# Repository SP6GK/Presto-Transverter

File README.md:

# Presto — QO-100 Transverter

**Status: Work in Progress — October 2026**

Presto is a modular transverter designed to enable communication via the QO-100 satellite using a standard 10 m capable HF transceiver. It provides a 2.4 GHz S-band uplink and downconverts the Ku-band LNB signal for reception on an HF transceiver.

This project includes the schematic and PCB design files, organized under the `ECAD/` directory.
`Documents/` includes interactive BOM and .pdf schematic.

## Features

- **RF signal quality:** Multi-stage frequency conversion, filtering, and high linearity mixers to minimize spurious emissions.
- **Modular hardware:** Replaceable local oscillator modules, a dedicated control head, and extensive RF shielding.
- **LNB front end:** Band pass filtering, attenuation, a bypassable LNA, an integrated downconverter, and an output for an external SDR.
- **LNB control:** Programmable bias-T voltage for polarization selection.
- **Embedded firmware:** STM32F411 microcontroller running C with FreeRTOS.
- **Graphical interface:** Frequency control, configuration menus, and diagnostic information.
- **Remote control:** B.A.S.I.C. (Basic Automated SCPI Interpreter for Controllers) provides serial control through SCPI-like commands.
- **Built-in diagnostics:** Startup and runtime self-tests, error logging, memory integrity checks, and automatic gain control.
- **Calibration tools:** Python scripts and service commands for EEPROM programming and automated calibration.

## System and compatibility
This repository contains all documentation for the motherboard of Presto transverter. Complete system consists also requires:
- **Control Head** Contains mcu with software and HID
- **2 x LO Module** LMX2572 LP based local oscillator module
Repositories for above modules are coming soon

## Project Status

**This project is actively under development and is not yet complete.**
Currently the RF path is under evaluation and characterization.

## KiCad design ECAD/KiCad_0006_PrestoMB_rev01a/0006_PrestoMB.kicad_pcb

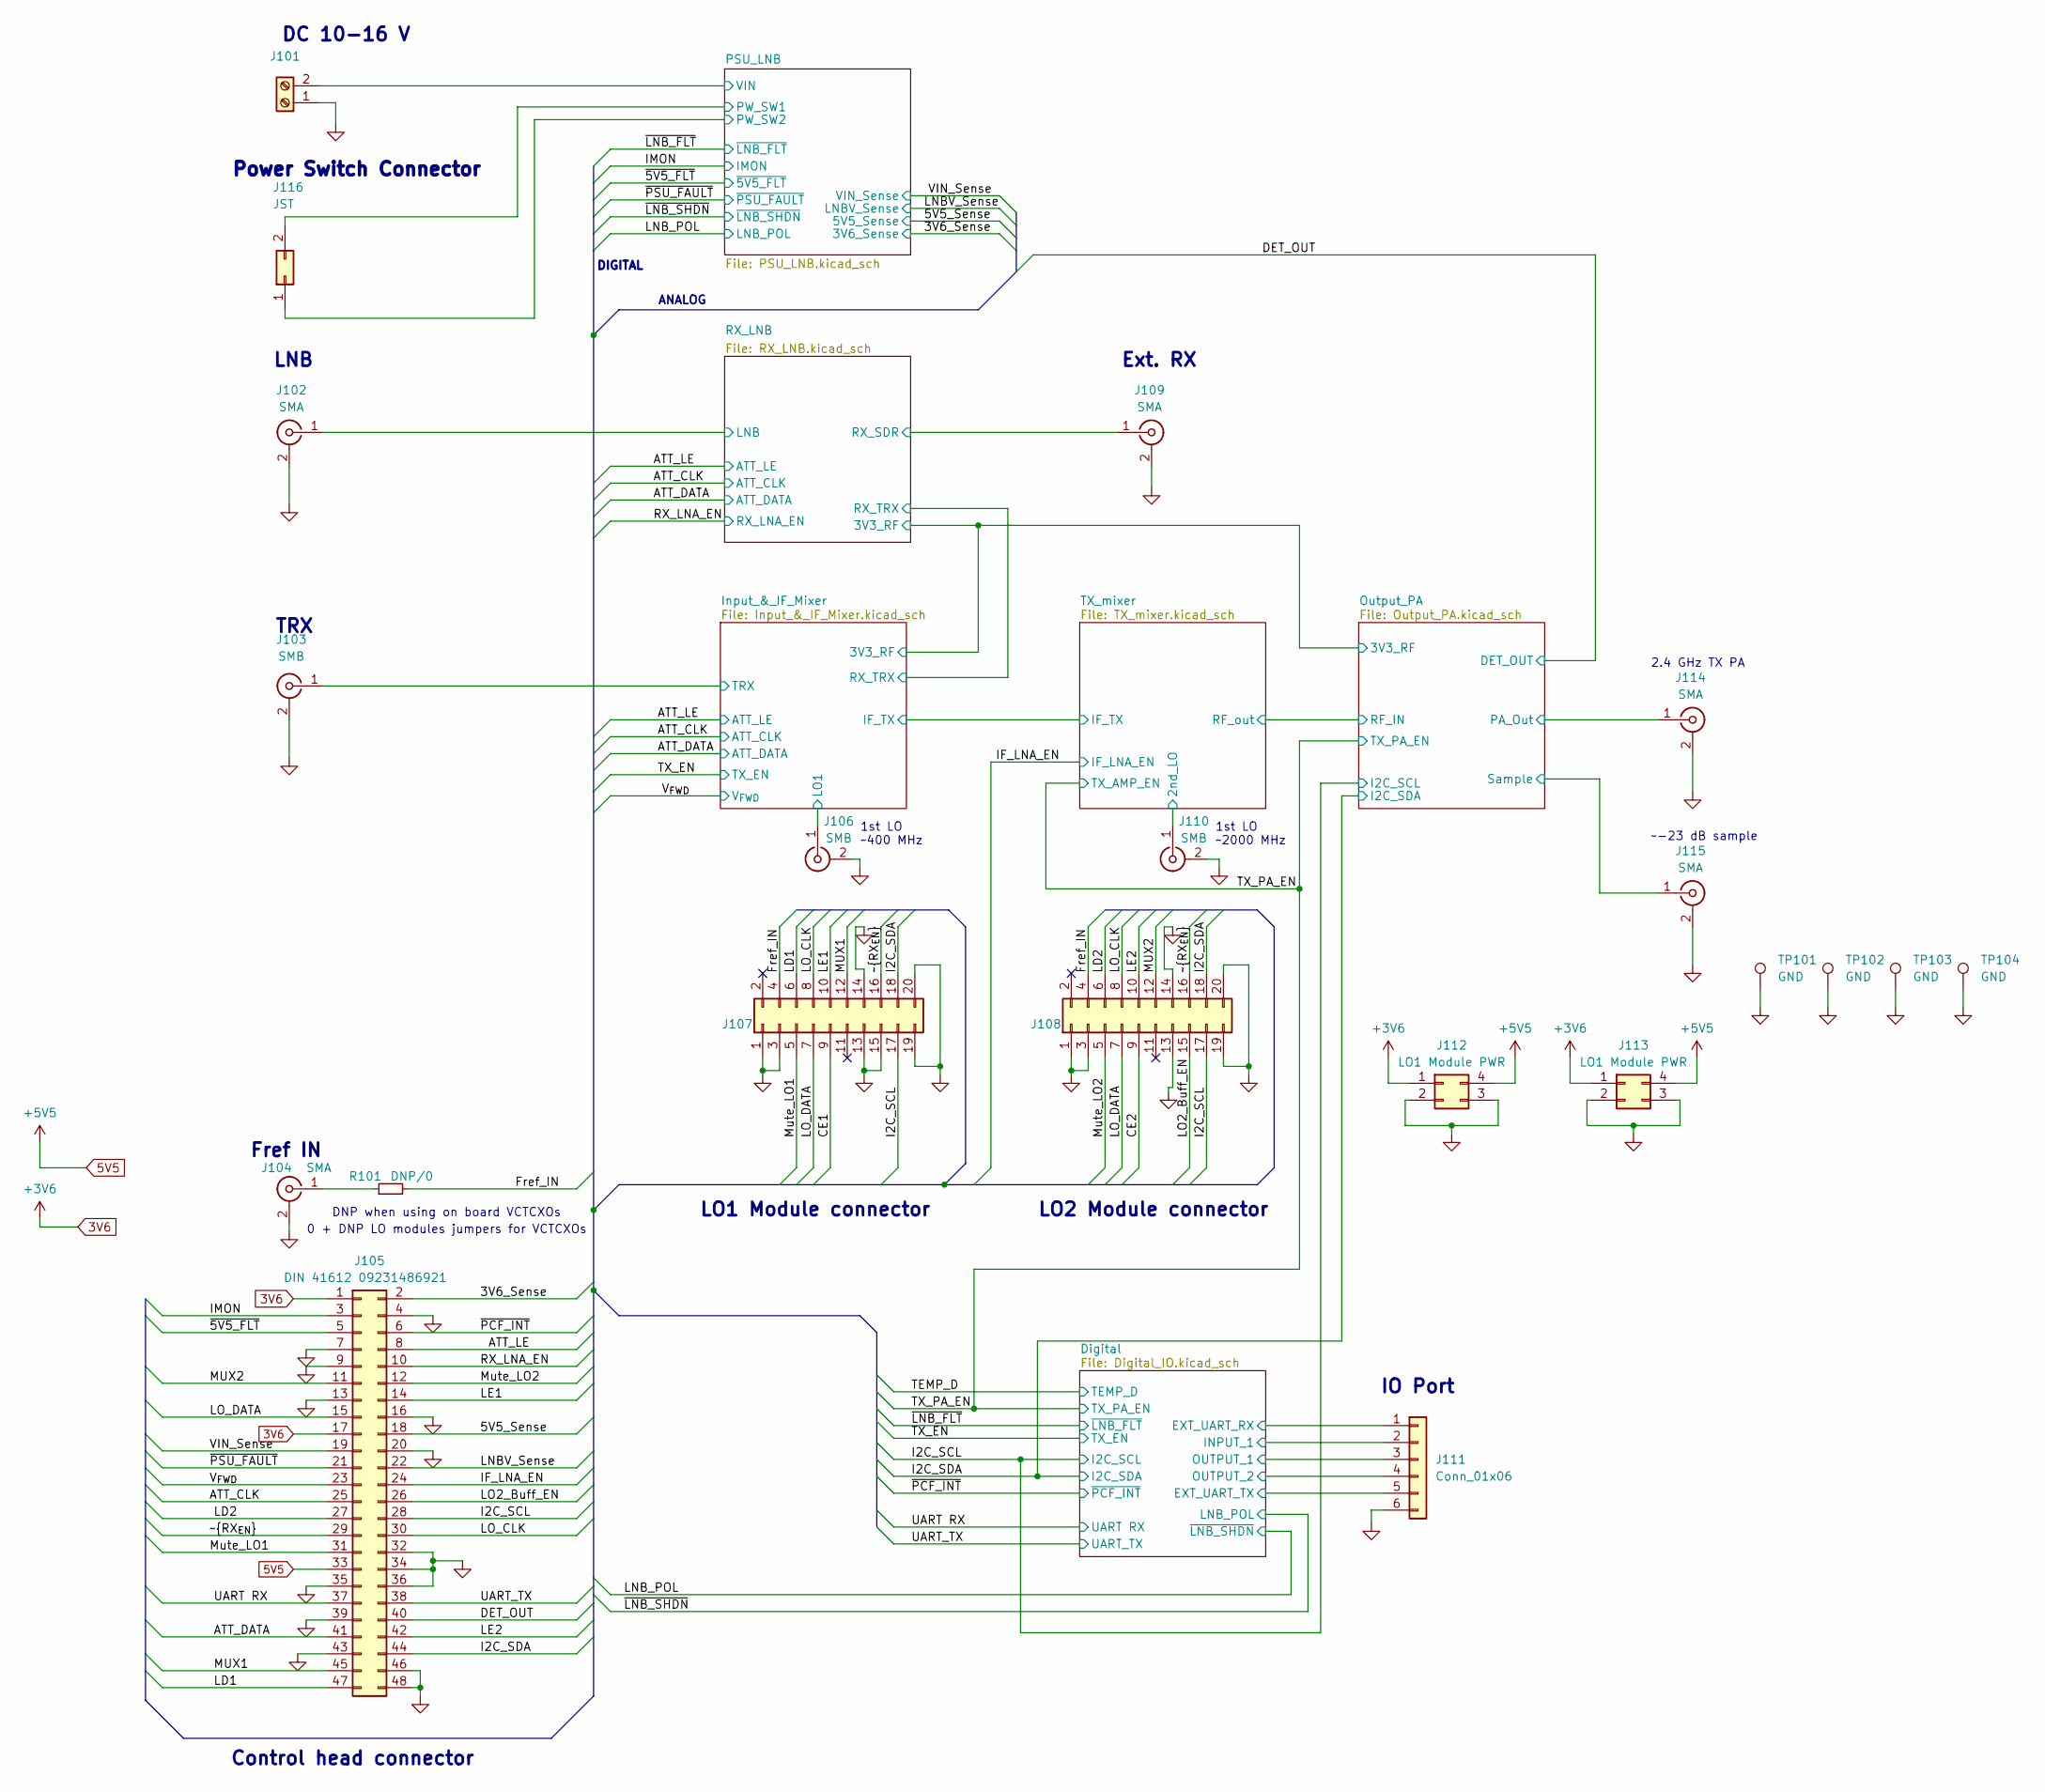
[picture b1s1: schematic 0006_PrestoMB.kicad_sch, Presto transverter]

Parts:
J101: Screw_Terminal_01x02; TerminalBlock_bornier-2_P5.08mm
J102, J114, J115: SMA; SMA_Samtec_SMA-J-P-H-ST-EM1_EdgeMount
J103, J106, J110: SMB; SMB_Jack_Vertical
J104, J109: SMA; SMB_Jack_Vertical
J105: DIN 41612 09231486921; DIN_41612_48Pin_90angle_Male_09231486921HARTING
J107, J108: LO1 Connector; PinHeader_2x10_P2.54mm_Vertical
J111: Conn_01x06; JST_EH_B6B-EH-A_1x06_P2.50mm_Vertical
J112, J113: LO1 Module PWR; PinHeader_2x02_P2.54mm_Vertical
J116: JST; JST_EH_B2B-EH-A_1x02_P2.50mm_Vertical
R101: DNP/0; R_1206_3216Metric_Pad1.30x1.75mm_HandSolder
TP101, TP102, TP103, TP104: GND; TestPoint_Pad_D4.0mm

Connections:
3V6: J105.1, J105.17, J112.1, J113.1; also elsewhere on the board
5V5: J105.33, J112.4, J113.4; also elsewhere on the board
/3V6_Sense: J105.2; also elsewhere on the board
/5V5_Sense: J105.18; also elsewhere on the board
/ATT_CLK: J105.25; also elsewhere on the board
/ATT_DATA: J105.41; also elsewhere on the board
/ATT_LE: J105.8; also elsewhere on the board
/CE1: J107.9
/CE2: J108.9
/DET_OUT: J105.40; also elsewhere on the board
/Digital/EXT_UART_RX: J111.1; also elsewhere on the board
/Digital/EXT_UART_TX: J111.5; also elsewhere on the board
/Digital/INPUT_1: J111.2; also elsewhere on the board
/Digital/OUTPUT_1: J111.3; also elsewhere on the board
/Digital/OUTPUT_2: J111.4; also elsewhere on the board
/Fref_IN: J107.4, J108.4, R101.2
/I2C_SCL: J105.28, J107.17, J108.17; also elsewhere on the board
/I2C_SDA: J105.44, J107.18, J108.18; also elsewhere on the board
/IF_LNA_EN: J105.24; also elsewhere on the board
/IMON: J105.3; also elsewhere on the board
/Input_&_IF_Mixer/LO1: J106.1 (In); also elsewhere on the board
/Input_&_IF_Mixer/TRX: J103.1 (In); also elsewhere on the board
/LD1: J105.47, J107.6
/LD2: J105.27, J108.6
/LE1: J105.14, J107.10
/LE2: J105.42, J108.10
/LNBV_Sense: J105.22; also elsewhere on the board
/LO2_Buff_EN: J105.26, J108.15
/LO_CLK: J105.30, J107.8, J108.8
/LO_DATA: J105.15, J107.7, J108.7
/MUX1: J105.45, J107.12
/MUX2: J105.11, J108.12
/Mute_LO1: J105.31, J107.5
/Mute_LO2: J105.12, J108.5
/Output_PA/PA_Out: J114.1 (In); also elsewhere on the board
/Output_PA/Sample: J115.1 (In); also elsewhere on the board
/PSU_LNB/PW_SW1: J116.2; also elsewhere on the board
/PSU_LNB/PW_SW2: J116.1; also elsewhere on the board
/PSU_LNB/VIN: J101.2; also elsewhere on the board
/RX_LNA_EN: J105.10; also elsewhere on the board
/RX_LNB/LNB: J102.1 (In); also elsewhere on the board
/RX_LNB/RX_SDR: J109.1 (In); also elsewhere on the board
/TX_mixer/2nd_LO: J110.1 (In); also elsewhere on the board
/UART RX: J105.37; also elsewhere on the board
/UART_TX: J105.38; also elsewhere on the board
/VIN_Sense: J105.19; also elsewhere on the board
/V_{FWD}: J105.23; also elsewhere on the board
/~5V5_FLT: J105.5; also elsewhere on the board
/~PCF_INT: J105.6; also elsewhere on the board
/~PSU_FAULT: J105.21; also elsewhere on the board
/~RX_{EN}: J105.29, J107.16, J108.16
GND: J101.1, J102.2 (Ext), J103.2 (Ext), J104.2 (Ext), J105.4, J105.7, J105.9, J105.13, J105.16, J105.20, J105.32, J105.34, J105.35, J105.36, J105.39, J105.43, J105.46, J105.48, J106.2 (Ext), J107.1, J107.3, J107.13, J107.14, J107.15, J107.19, J107.20, J108.1, J108.3, J108.13, J108.14, J108.19, J108.20, J109.2 (Ext), J110.2 (Ext), J111.6, J112.2, J112.3, J113.2, J113.3, J114.2 (Ext), J115.2 (Ext), TP101.1, TP102.1, TP103.1, TP104.1; also elsewhere on the board
unnamed: J104.1 (In), R101.1

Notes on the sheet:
1st LO ~400 MHz
DIGITAL
Control head connector
Power Switch Connector
LO1 Module connector
DNP when using on board VCTCXOs
LNB
Fref IN
2.4 GHz TX PA
ANALOG
TRX
IO Port
LO2 Module connector
Ext. RX
DC 10-16 V
~-23 dB sample
1st LO ~2000 MHz
0 + DNP LO modules jumpers for VCTCXOs

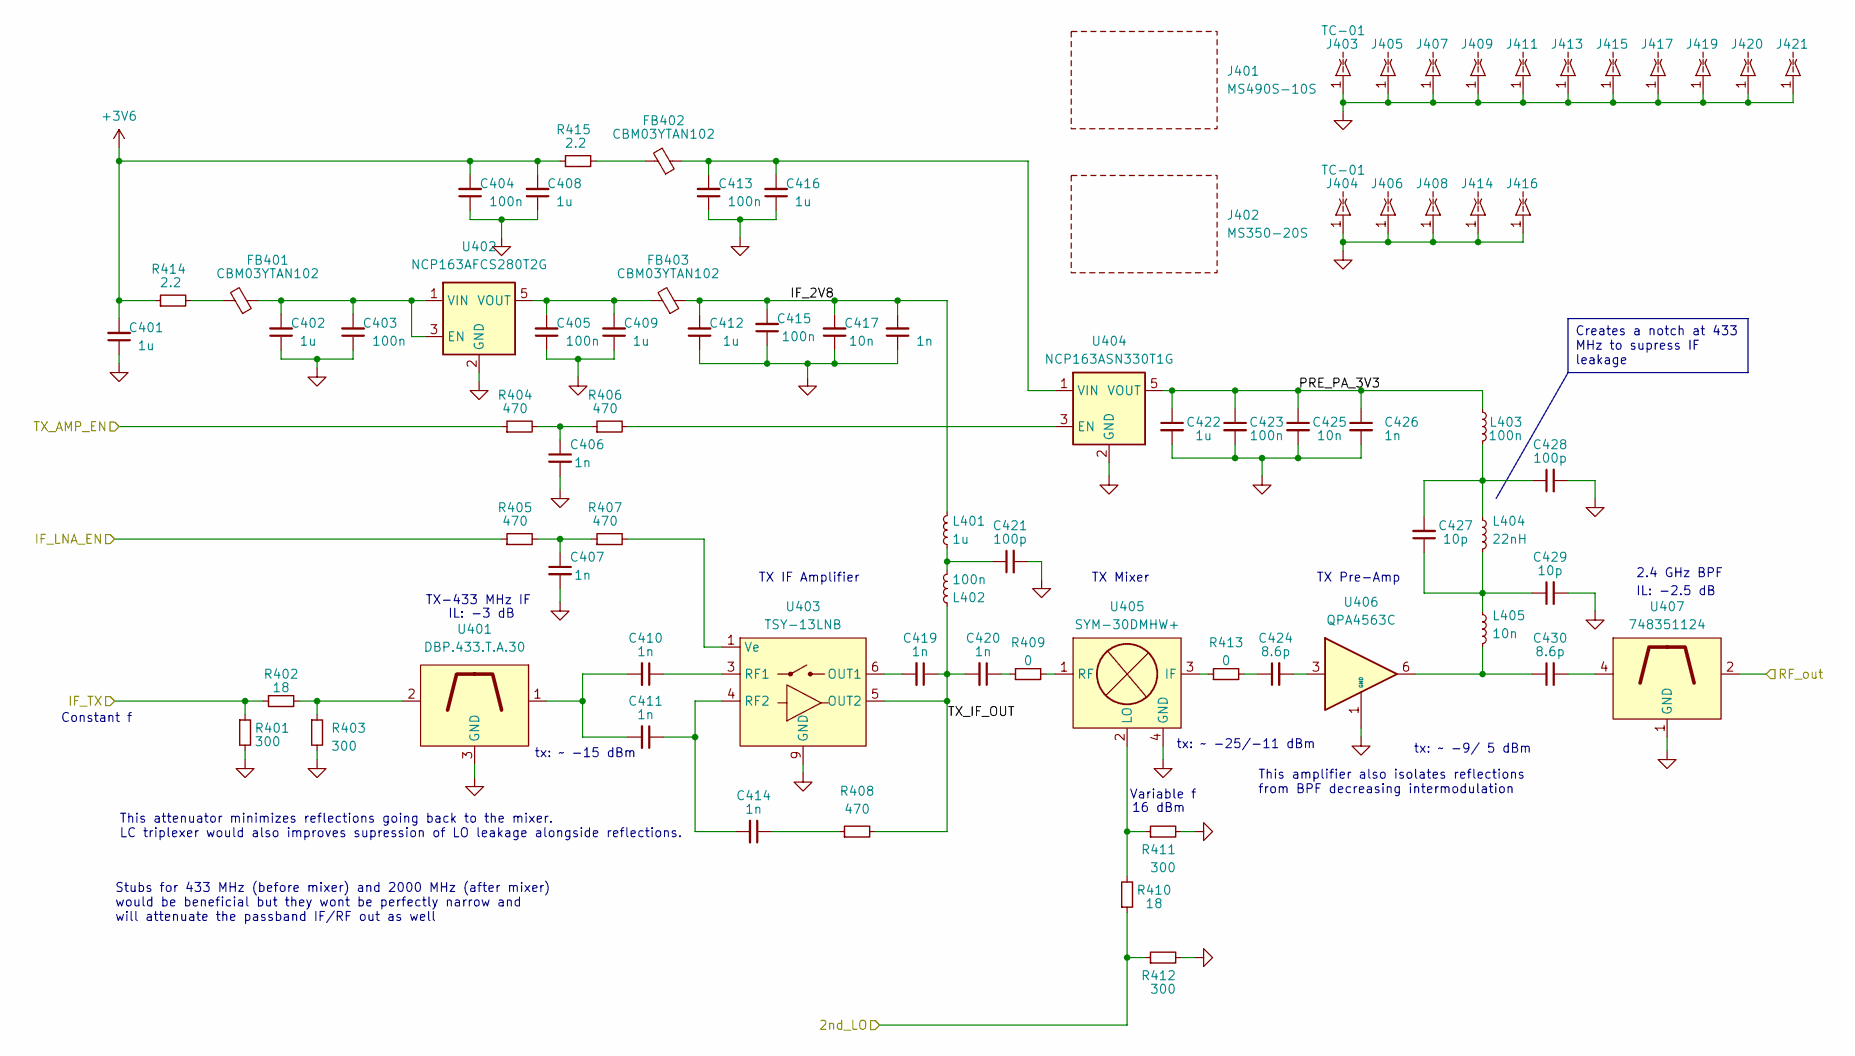
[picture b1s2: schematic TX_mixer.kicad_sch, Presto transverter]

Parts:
C401, C402, C408, C409, C412, C416, C422: 1u; C_0603_1608Metric_Pad1.08x0.95mm_HandSolder
C403, C404, C405, C413, C415, C423: 100n; C_0603_1608Metric_Pad1.08x0.95mm_HandSolder
C406, C407, C410, C411, C414, C418, C419, C420, C426: 1n; C_0603_1608Metric_Pad1.08x0.95mm_HandSolder
C417, C425: 10n; C_0603_1608Metric_Pad1.08x0.95mm_HandSolder
C421, C428: 100p; C_0603_1608Metric_Pad1.08x0.95mm_HandSolder
C424, C430: 8.6p; C_0603_1608Metric_Pad1.08x0.95mm_HandSolder
C427, C429: 10p; C_0603_1608Metric_Pad1.08x0.95mm_HandSolder
FB401, FB402, FB403: CBM03YTAN102; L_0603_1608Metric_Pad1.05x0.95mm_HandSolder
J401: MS490S-10S; MS490_Shield
J402: MS350-20S; MS323-30S-NS
J403, J404, J419, J421: TC-01; TC-01_CLIP_LeaderTech_half
J405, J406, J407, J408, J409, J411, J413, J414, J415, J416, J417, J420: TC-01; TC-01_CLIP_LeaderTech
L401: 1u; L_0805_2012Metric_Pad1.05x1.20mm_HandSolder
L402, L403: 100n; L_0603_1608Metric_Pad1.05x0.95mm_HandSolder
L404: 22nH; L_0603_1608Metric_Pad1.05x0.95mm_HandSolder
L405: 10n; L_0603_1608Metric_Pad1.05x0.95mm_HandSolder
R401, R403, R411, R412: 300; R_0603_1608Metric_Pad0.98x0.95mm_HandSolder
R402, R410: 18; R_0603_1608Metric_Pad0.98x0.95mm_HandSolder
R404, R406, R408: 470; R_0603_1608Metric_Pad0.98x0.95mm_HandSolder
R405, R407: 470; R_0402_1005Metric_Pad0.72x0.64mm_HandSolder
R409, R413: 0; R_1206_3216Metric_Pad1.30x1.75mm_HandSolder
R414, R415: 2.2; R_0603_1608Metric_Pad0.98x0.95mm_HandSolder
U401: DBP.433.T.A.30; TAOGLAS_DBP_433
U402: NCP163AFCS280T2G; SOT-23-5
U403: TSY-13LNB; MiniCircuits_MC163_TSY13LNB
U404: NCP163ASN330T1G; SOT-23-5
U405: SYM-30DMHW+; SYM-18H+
U406: QPA4563C; SOT-363_SC-70-6_Handsoldering
U407: 748351124; Wurth_BPF_2400_nr748351124

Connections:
3V6: C401.2, C404.2, C408.2, R414.1, R415.1; also elsewhere on the board
/IF_LNA_EN: R405.1; also elsewhere on the board
/Input_&_IF_Mixer/IF_TX: R401.1, R402.1; also elsewhere on the board
/Output_PA/RF_IN: U407.2; also elsewhere on the board
/TX_PA_EN: R404.1; also elsewhere on the board
/TX_mixer/2nd_LO: R410.1, R412.1; also elsewhere on the board
/TX_mixer/IF_2V8: C412.2, C415.2, C417.2, C418.2, FB403.1, L401.1
/TX_mixer/PRE_PA_3V3: C422.1, C423.1, C425.1, C426.1, L403.1, U404.5 (VOUT)
/TX_mixer/TX_IF_OUT: C419.1, C420.2, L402.2, R408.2, U403.5 (OUT2)
GND: C401.1, C402.1, C403.1, C404.1, C405.1, C406.2, C407.2, C408.1, C409.1, C412.1, C413.1, C415.1, C416.1, C417.1, C418.1, C421.2, C422.2, C423.2, C425.2, C426.2, C428.2, C429.2, J403.1, J404.1, J405.1, J406.1, J407.1, J408.1, J409.1, J411.1, J413.1, J414.1, J415.1, J416.1, J417.1, J419.1, J420.1, J421.1, R401.2, R403.2, R411.2, R412.2, U401.3 (GND), U402.2 (GND), U403.2 (GND), U403.7 (GND), U403.8 (GND), U403.9 (GND), U404.2 (GND), U405.4 (GND), U405.5 (GND), U405.6 (GND), U406.1 (GND), U406.2 (GND), U406.4 (GND), U406.5 (GND), U407.1 (GND), U407.3 (GND); also elsewhere on the board
unnamed: C406.1, R404.2, R406.1
unnamed: C407.1, R405.2, R407.1
unnamed: C410.2, C411.2, U401.1
unnamed: C414.1, R408.1
unnamed: C420.1, R409.1
unnamed: C421.1, L401.2, L402.1
unnamed: C424.1, R413.2
unnamed: C424.2, U406.3
unnamed: C427.1, C429.1, L404.2, L405.1
unnamed: C427.2, C428.1, L403.2, L404.1
unnamed: C430.1, L405.2, U406.6
unnamed: C430.2, U407.4
unnamed: FB401.2, R414.2
unnamed: FB402.2, R415.2
unnamed: R402.2, R403.1, U401.2
unnamed: C402.2, C403.2, FB401.1, U402.1 (VIN), U402.3 (EN)
unnamed: C405.2, C409.2, FB403.2, U402.5 (VOUT)
unnamed: C419.2, U403.6 (OUT1)
unnamed: C410.1, U403.3 (RF1)
unnamed: C411.1, C414.2, U403.4 (RF2)
unnamed: R407.2, U403.1 (Ve)
unnamed: R406.2, U404.3 (EN)
unnamed: C413.2, C416.2, FB402.1, U404.1 (VIN)
unnamed: R413.1, U405.3 (IF)
unnamed: R410.2, R411.1, U405.2 (LO)
unnamed: R409.2, U405.1 (RF)

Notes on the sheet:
Variable f
This amplifier also isolates reflections from BPF decreasing intermodulation
2.4 GHz BPF
TX-433 MHz IF
TX Mixer
16 dBm
This attenuator minimizes reflections going back to the mixer. LC triplexer would also improves supression of LO leakage alongside reflections.
tx: ~ -15 dBm
IL: -3 dB
IL: -2.5 dB
Stubs for 433 MHz (before mixer) and 2000 MHz (after mixer) would be beneficial but they wont be perfectly narrow and will attenuate the passband IF/RF out as well
TX Pre-Amp
tx: ~ -9/ 5 dBm
Constant f
tx: ~ -25/-11 dBm
TX IF Amplifier
Creates a notch at 433 MHz to supress IF leakage

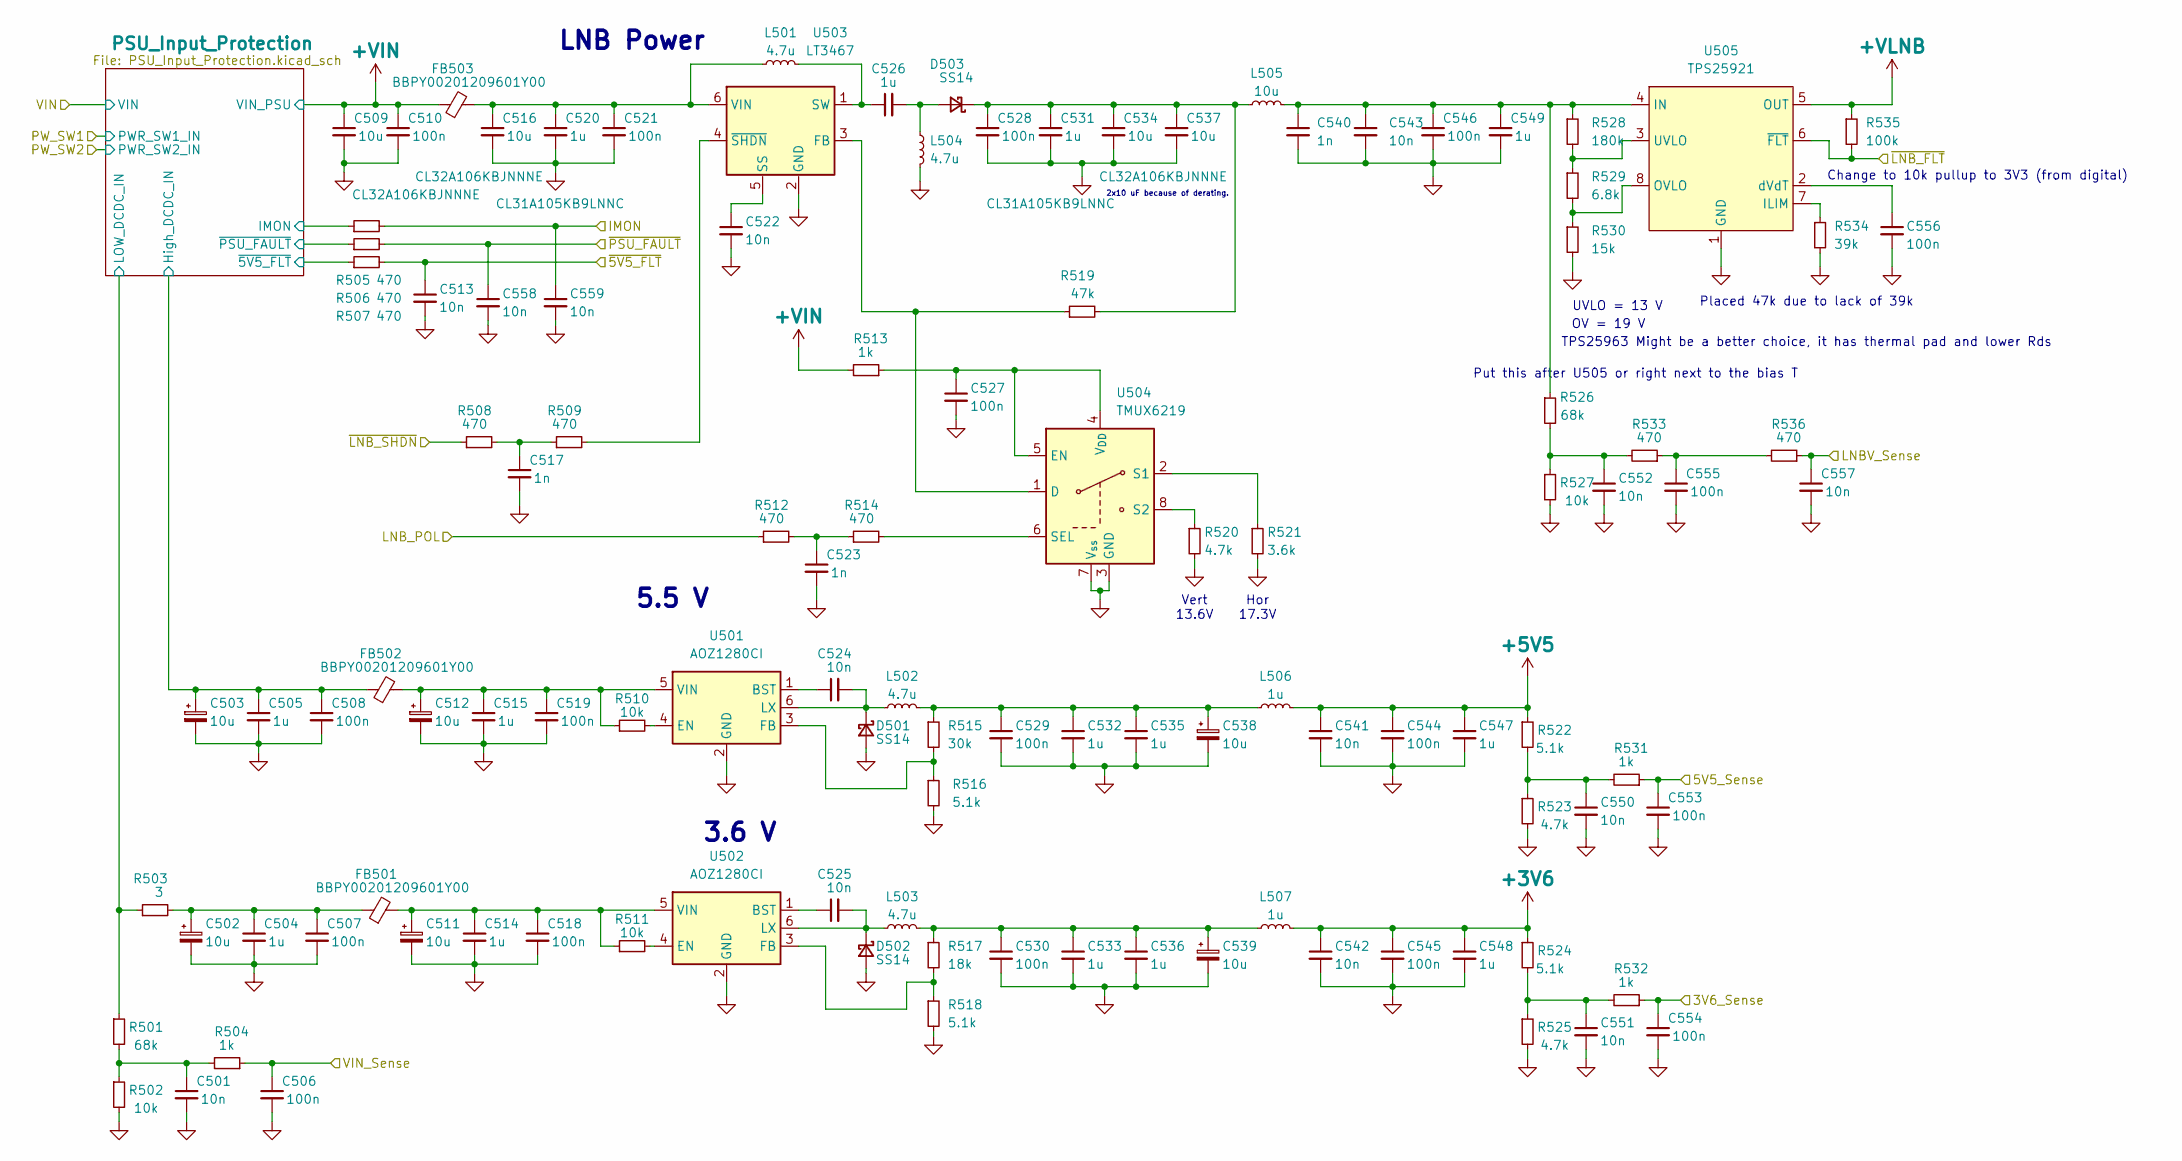
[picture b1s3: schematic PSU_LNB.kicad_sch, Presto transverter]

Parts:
C501, C524, C525, C542, C550, C551, C552: 10n; C_0603_1608Metric_Pad1.08x0.95mm_HandSolder
C502, C503, C511, C512, C538, C539: 10u; C_1206_3216Metric_Pad1.33x1.80mm_HandSolder
C504, C505, C514, C515, C526, C532, C533, C535, C536, C547, C548: 1u; C_0805_2012Metric_Pad1.18x1.45mm_HandSolder
C506, C545, C553, C554, C555: 100n; C_0603_1608Metric_Pad1.08x0.95mm_HandSolder
C507, C508, C510, C518, C519, C521, C527, C528, C529, C530, C544, C546, C556: 100n; C_0805_2012Metric_Pad1.18x1.45mm_HandSolder
C509, C516, C534, C537: 10u; C_1210_3225Metric_Pad1.33x2.70mm_HandSolder
C513, C557, C558, C559: 10n; C_0402_1005Metric_Pad0.74x0.62mm_HandSolder
C517, C523: 1n; C_0603_1608Metric_Pad1.08x0.95mm_HandSolder
C520, C531, C549: 1u; C_1206_3216Metric_Pad1.33x1.80mm_HandSolder
C522, C541, C543: 10n; C_0805_2012Metric_Pad1.18x1.45mm_HandSolder
C540: 1n; C_0805_2012Metric_Pad1.18x1.45mm_HandSolder
D501, D502, D503: SS14; D_SMA
FB501, FB502, FB503: BBPY00201209601Y00; L_0805_2012Metric_Pad1.05x1.20mm_HandSolder
L501, L502, L503, L504: 4.7u; L_6.3x6.3_H3
L505: 10u; LED_0805_2012Metric
L506, L507: 1u; LED_0805_2012Metric
R501, R526: 68k; R_0805_2012Metric_Pad1.20x1.40mm_HandSolder
R502, R527: 10k; R_0805_2012Metric_Pad1.20x1.40mm_HandSolder
R503: 3; R_1206_3216Metric_Pad1.30x1.75mm_HandSolder
R504, R513, R531, R532: 1k; R_0603_1608Metric_Pad0.98x0.95mm_HandSolder
R505, R506, R507, R536: 470; R_0402_1005Metric_Pad0.72x0.64mm_HandSolder
R508, R509, R512, R514, R533: 470; R_0603_1608Metric_Pad0.98x0.95mm_HandSolder
R510, R511: 10k; R_0603_1608Metric_Pad0.98x0.95mm_HandSolder
R515: 30k; R_0603_1608Metric_Pad0.98x0.95mm_HandSolder
R516, R518, R522, R524: 5.1k; R_0603_1608Metric_Pad0.98x0.95mm_HandSolder
R517: 18k; R_0603_1608Metric_Pad0.98x0.95mm_HandSolder
R519: 47k; R_0603_1608Metric_Pad0.98x0.95mm_HandSolder
R520, R523, R525: 4.7k; R_0603_1608Metric_Pad0.98x0.95mm_HandSolder
R521: 3.6k; R_0603_1608Metric_Pad0.98x0.95mm_HandSolder
R528: 180k; R_0805_2012Metric_Pad1.20x1.40mm_HandSolder
R529: 6.8k; R_0805_2012Metric_Pad1.20x1.40mm_HandSolder
R530: 15k; R_0805_2012Metric_Pad1.20x1.40mm_HandSolder
R534: 39k; R_0603_1608Metric_Pad0.98x0.95mm_HandSolder
R535: 100k; R_0603_1608Metric_Pad0.98x0.95mm_HandSolder
U501, U502: AOZ1280CI; SOT-23-6
U503: LT3467; TSOT-23-6_HandSoldering
U504: TMUX6219; VSSOP8_3x3mm
U505: TPS25921; SOIC8_EP_3.9x4.9P1.27

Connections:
3V6: C542.1, C545.1, C548.1, L507.2, R524.1; also elsewhere on the board
5V5: C541.1, C544.1, C547.1, L506.2, R522.1; also elsewhere on the board
+VIN: C509.1, C510.1, FB503.1, R501.1, R503.1, R513.2; also elsewhere on the board
+VLNB: R535.1, U505.5 (OUT); also elsewhere on the board
/3V6_Sense: C554.1, R532.1; also elsewhere on the board
/5V5_Sense: C553.1, R531.1; also elsewhere on the board
/IMON: C559.1, R505.2; also elsewhere on the board
/LNBV_Sense: C557.1, R536.1; also elsewhere on the board
/LNB_POL: R512.1; also elsewhere on the board
/PSU_LNB/PSU_Input_Protection/High_DCDC_IN: C503.1, C505.1, C508.1, FB502.1; also elsewhere on the board
/PSU_LNB/PSU_Input_Protection/IMON: R505.1; also elsewhere on the board
/PSU_LNB/PSU_Input_Protection/~5V5_FLT: R507.1; also elsewhere on the board
/PSU_LNB/PSU_Input_Protection/~PSU_FAULT: R506.1; also elsewhere on the board
/VIN_Sense: C506.1, R504.1; also elsewhere on the board
/~5V5_FLT: C513.1, R507.2; also elsewhere on the board
/~LNB_FLT: R535.2, U505.6 (~FLT); also elsewhere on the board
/~LNB_SHDN: R508.1; also elsewhere on the board
/~PSU_FAULT: C558.1, R506.2; also elsewhere on the board
GND: C501.2, C502.2, C503.2, C504.2, C505.2, C506.2, C507.2, C508.2, C509.2, C510.2, C511.2, C512.2, C513.2, C514.2, C515.2, C516.2, C517.2, C518.2, C519.2, C520.2, C521.2, C522.2, C523.2, C527.2, C528.2, C529.2, C530.2, C531.2, C532.2, C533.2, C534.2, C535.2, C536.2, C537.2, C538.2, C539.2, C540.2, C541.2, C542.2, C543.2, C544.2, C545.2, C546.2, C547.2, C548.2, C549.2, C550.2, C551.2, C552.2, C553.2, C554.2, C555.2, C556.2, C557.2, C558.2, C559.2, D501.2 (A), D502.2 (A), L504.2, R502.2, R516.2, R518.2, R520.2, R521.2, R523.2, R525.2, R527.2, R530.2, R534.2, U501.2 (GND), U502.2 (GND), U503.2 (GND), U504.3 (GND), U504.7 (V_{ss}), U505.1 (GND), U505.9 (GND); also elsewhere on the board
unnamed: C501.1, R501.2, R502.1, R504.2
unnamed: C502.1, C504.1, C507.1, FB501.1, R503.2
unnamed: C517.1, R508.2, R509.1
unnamed: C523.1, R512.2, R514.1
unnamed: C529.1, C532.1, C535.1, C538.1, L502.2, L506.1, R515.1
unnamed: C530.1, C533.1, C536.1, C539.1, L503.2, L507.1, R517.1
unnamed: C550.1, R522.2, R523.1, R531.2
unnamed: C551.1, R524.2, R525.1, R532.2
unnamed: C552.1, R526.2, R527.1, R533.2
unnamed: C555.1, R533.1, R536.2
unnamed: C524.2, D501.1 (K), L502.1, U501.6 (LX)
unnamed: C525.2, D502.1 (K), L503.1, U502.6 (LX)
unnamed: C526.2, D503.2 (A), L504.1
unnamed: C528.1, C531.1, C534.1, C537.1, D503.1 (K), L505.1, R519.2
unnamed: C524.1, U501.1 (BST)
unnamed: R510.2, U501.4 (EN)
unnamed: R515.2, R516.1, U501.3 (FB)
unnamed: C512.1, C515.1, C519.1, FB502.2, R510.1, U501.5 (VIN)
unnamed: C525.1, U502.1 (BST)
unnamed: R511.2, U502.4 (EN)
unnamed: R517.2, R518.1, U502.3 (FB)
unnamed: C511.1, C514.1, C518.1, FB501.2, R511.1, U502.5 (VIN)
unnamed: R519.1, U503.3 (FB), U504.1 (D)
unnamed: C522.1, U503.5 (SS)
unnamed: C526.1, L501.2, U503.1 (SW)
unnamed: C516.1, C520.1, C521.1, FB503.2, L501.1, U503.6 (VIN)
unnamed: R509.2, U503.4 (~SHDN)
unnamed: C527.1, R513.1, U504.4 (V_{DD}), U504.5 (EN)
unnamed: R521.1, U504.2 (S1)
unnamed: R520.1, U504.8 (S2)
unnamed: R514.2, U504.6 (SEL)
unnamed: R534.1, U505.7 (ILIM)
unnamed: C540.1, C543.1, C546.1, C549.1, L505.2, R526.1, R528.1, U505.4 (IN)
unnamed: R529.2, R530.1, U505.8 (OVLO)
unnamed: R528.2, R529.1, U505.3 (UVLO)
unnamed: C556.1, U505.2 (dVdT)

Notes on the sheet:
5.5 V
TPS25963 Might be a better choice, it has thermal pad and lower Rds
Placed 47k due to lack of 39k
Vert 13.6V
Put this after U505 or right next to the bias T
UVLO = 13 V
Hor 17.3V
2x10 uF because of derating.
LNB Power
3.6 V
Change to 10k pullup to 3V3 (from digital)
OV = 19 V
